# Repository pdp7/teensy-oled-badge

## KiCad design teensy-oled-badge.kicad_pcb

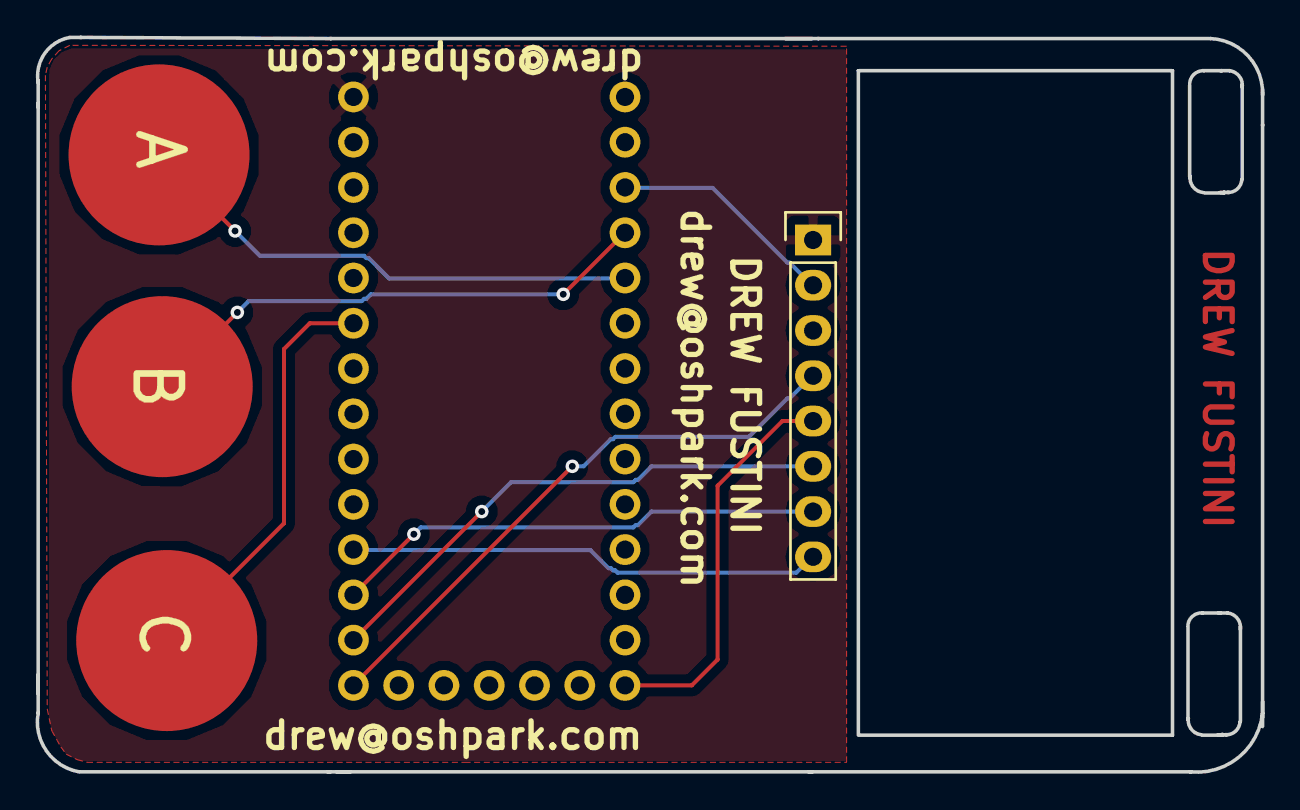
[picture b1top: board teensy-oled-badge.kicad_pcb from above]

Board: 2 copper layers, 68.7 x 41.2 mm, 5 parts (0 on the bottom side), 10 nets.

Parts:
CAP1, CAP2, CAP3: CAPSENSE_CIRCLE; CAPSENSE_CIRCLE_D10
J1: TEENSY-LC
J2: OLED_128x64; Pin_Header_Straight_1x08

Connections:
/CLK: J1.10, J2.7
/CS: J1.12, J2.4
/DC: J1.11, J2.6
/Data: J1.9, J2.8
/GND: J1.G1, J2.1
/RST: J1.13, J2.5
/VIN: J1.3V2, J2.2
unnamed: CAP1.1, J1.22
unnamed: CAP2.1, J1.23
unnamed: CAP3.1, J1.4

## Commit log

2016-09-20 add intial design files
2016-09-20 initial draft of layout
2016-09-20 fix DRC errors
2016-09-20 remove uneeded text
2016-09-20 adjust silkscreen text alignment
